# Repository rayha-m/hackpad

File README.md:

# Hackpad: 3 keys + a volume knob

A small macropad built for Hack Club's [Hackpad](https://hackpad.hackclub.com) program. It has three mechanical keys for copy, paste and undo, plus a rotary encoder knob that controls volume (turn) and mute (press). It runs custom QMK firmware on a Seeed XIAO RP2040.

## Features
- 3 × MX-style keys: Cmd+C, Cmd+V, Cmd+Z (easy to remap in `Firmware/hackpad/keymaps/default/keymap.c`)
- 1 × EC11 rotary encoder: volume down/up, press to mute
- Direct-pin wiring, so no diodes are needed
- 2-layer PCB, 21 × 80 mm
- 3D-printed sandwich-mount case (bottom + top plate), 100.85 × 41.8 × 16 mm

## Schematic

## PCB

The XIAO is mounted on the back of the board, behind SW1, following the Hackpad guide.

| Part | XIAO pin | RP2040 GPIO |
|---|---|---|
| SW1 (top key) | 11 (D10) | GP3 |
| SW2 | 10 (D9) | GP4 |
| SW3 | 9 (D8) | GP2 |
| Encoder A | 3 (D2) | GP28 |
| Encoder B | 2 (D1) | GP27 |
| Encoder push | 1 (D0) | GP26 |
| GND (all switches, encoder C & S2) | 13 | GND |

## Case

The case has two printed parts that sandwich the PCB:
- **Bottom**: 13 mm tall tray with a 3 mm floor, a pocket for the PCB (0.4 mm clearance per side) and a USB-C cutout at the XIAO end.
- **Top**: 3 mm plate with 14 × 14 mm openings for the three switches and the knob.

Four M3 screws go through the corners to hold the two parts together.

## Firmware
QMK firmware lives in `Firmware/hackpad`. To build it:

```
qmk compile -kb hackpad -km default
```

To flash it, hold the XIAO's BOOT button while plugging it in, then drag `production/firmware.uf2` onto the `RPI-RP2` drive.

## Bill of materials (BOM)

| Qty | Part | Notes |
|---|---|---|
| 1 | Seeed Studio XIAO RP2040 | Through-hole, mounted on the back of the PCB |
| 3 | MX-style mechanical switches | |
| 3 | 1u keycaps | |
| 1 | EC11 rotary encoder with push switch | Alps EC11E footprint |
| 1 | Knob for the EC11 encoder | |
| 4 | M3 × 16 mm screws | Hold the plate to the bottom |
| 1 | PCB | 2 layers, 21 × 80 mm (`production/gerbers.zip`) |
| 1 | 3D-printed bottom | `production/Bottom.STEP` |
| 1 | 3D-printed top plate | `production/Top.STEP` |

## Repository layout
```
CAD/          full assembled model (hackpad.STEP) + FreeCAD source
PCB/          KiCad project (.kicad_pro, .kicad_sch, .kicad_pcb)
Firmware/     QMK source
production/   gerbers.zip, Top/Bottom.STEP, firmware.uf2
images/       screenshots for this README
```

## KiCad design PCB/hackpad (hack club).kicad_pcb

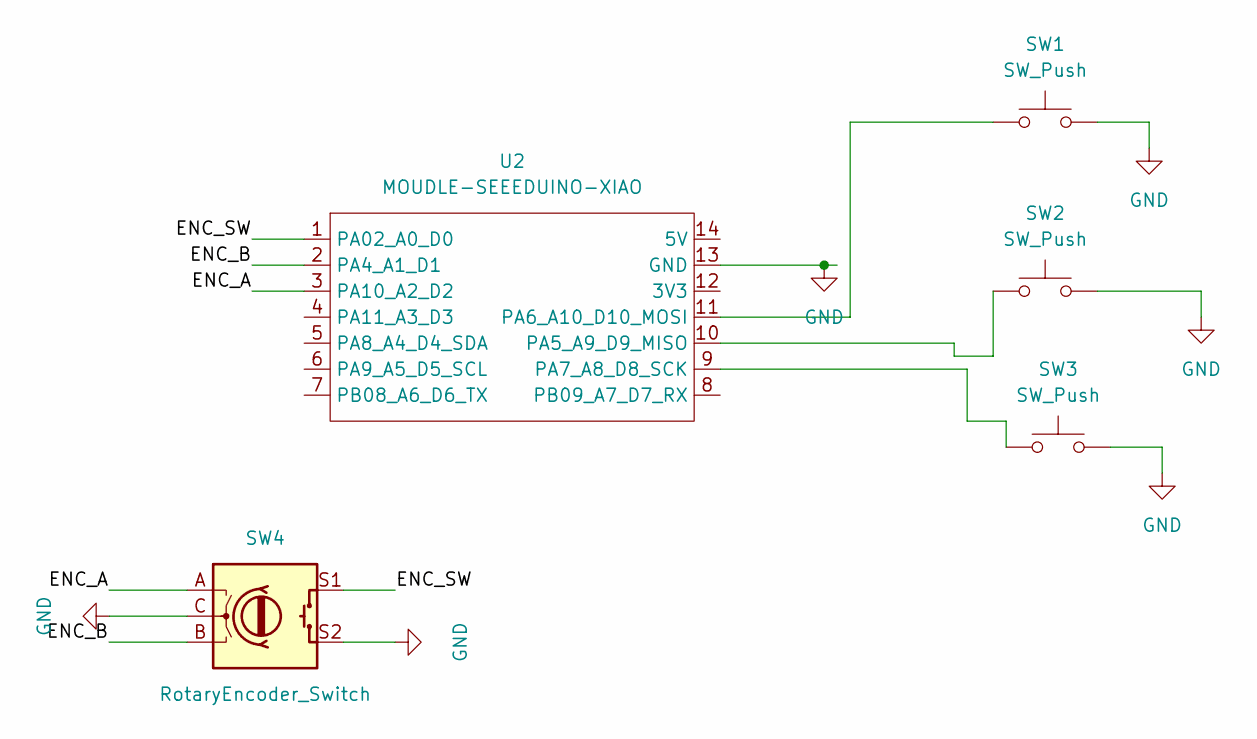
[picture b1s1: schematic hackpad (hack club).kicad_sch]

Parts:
SW1, SW2, SW3: SW_Push; SW_Cherry_MX_1.00u_PCB
SW4: RotaryEncoder_Switch; RotaryEncoder_Alps_EC11E-Switch_Vertical_H20mm
U2: MOUDLE-SEEEDUINO-XIAO; XIAO-RP2040-DIP

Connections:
/ENC_A: SW4.A, U2.3 (PA10_A2_D2)
/ENC_B: SW4.B, U2.2 (PA4_A1_D1)
/ENC_SW: SW4.S1, U2.1 (PA02_A0_D0)
GND: SW1.2, SW2.2, SW3.2, SW4.C, SW4.S2, U2.13 (GND)
unnamed: SW2.1, U2.10 (PA5_A9_D9_MISO)
unnamed: SW1.1, U2.11 (PA6_A10_D10_MOSI)
unnamed: SW3.1, U2.9 (PA7_A8_D8_SCK)

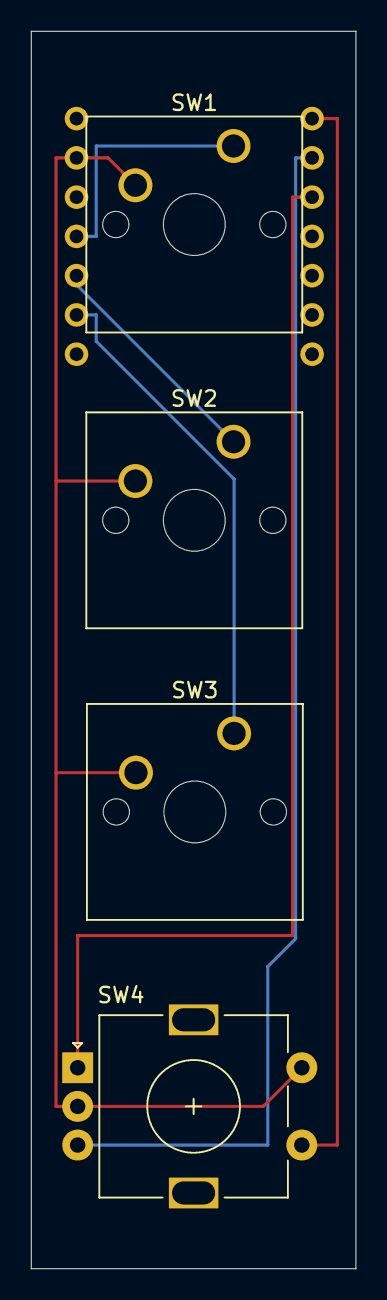
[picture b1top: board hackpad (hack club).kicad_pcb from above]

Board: 2 copper layers, 21.0 x 80.1 mm, 5 parts (1 on the bottom side), 7 nets.
